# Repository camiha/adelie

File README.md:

# adelie
 44key split keyboard   
 inspired by corne, caravelle

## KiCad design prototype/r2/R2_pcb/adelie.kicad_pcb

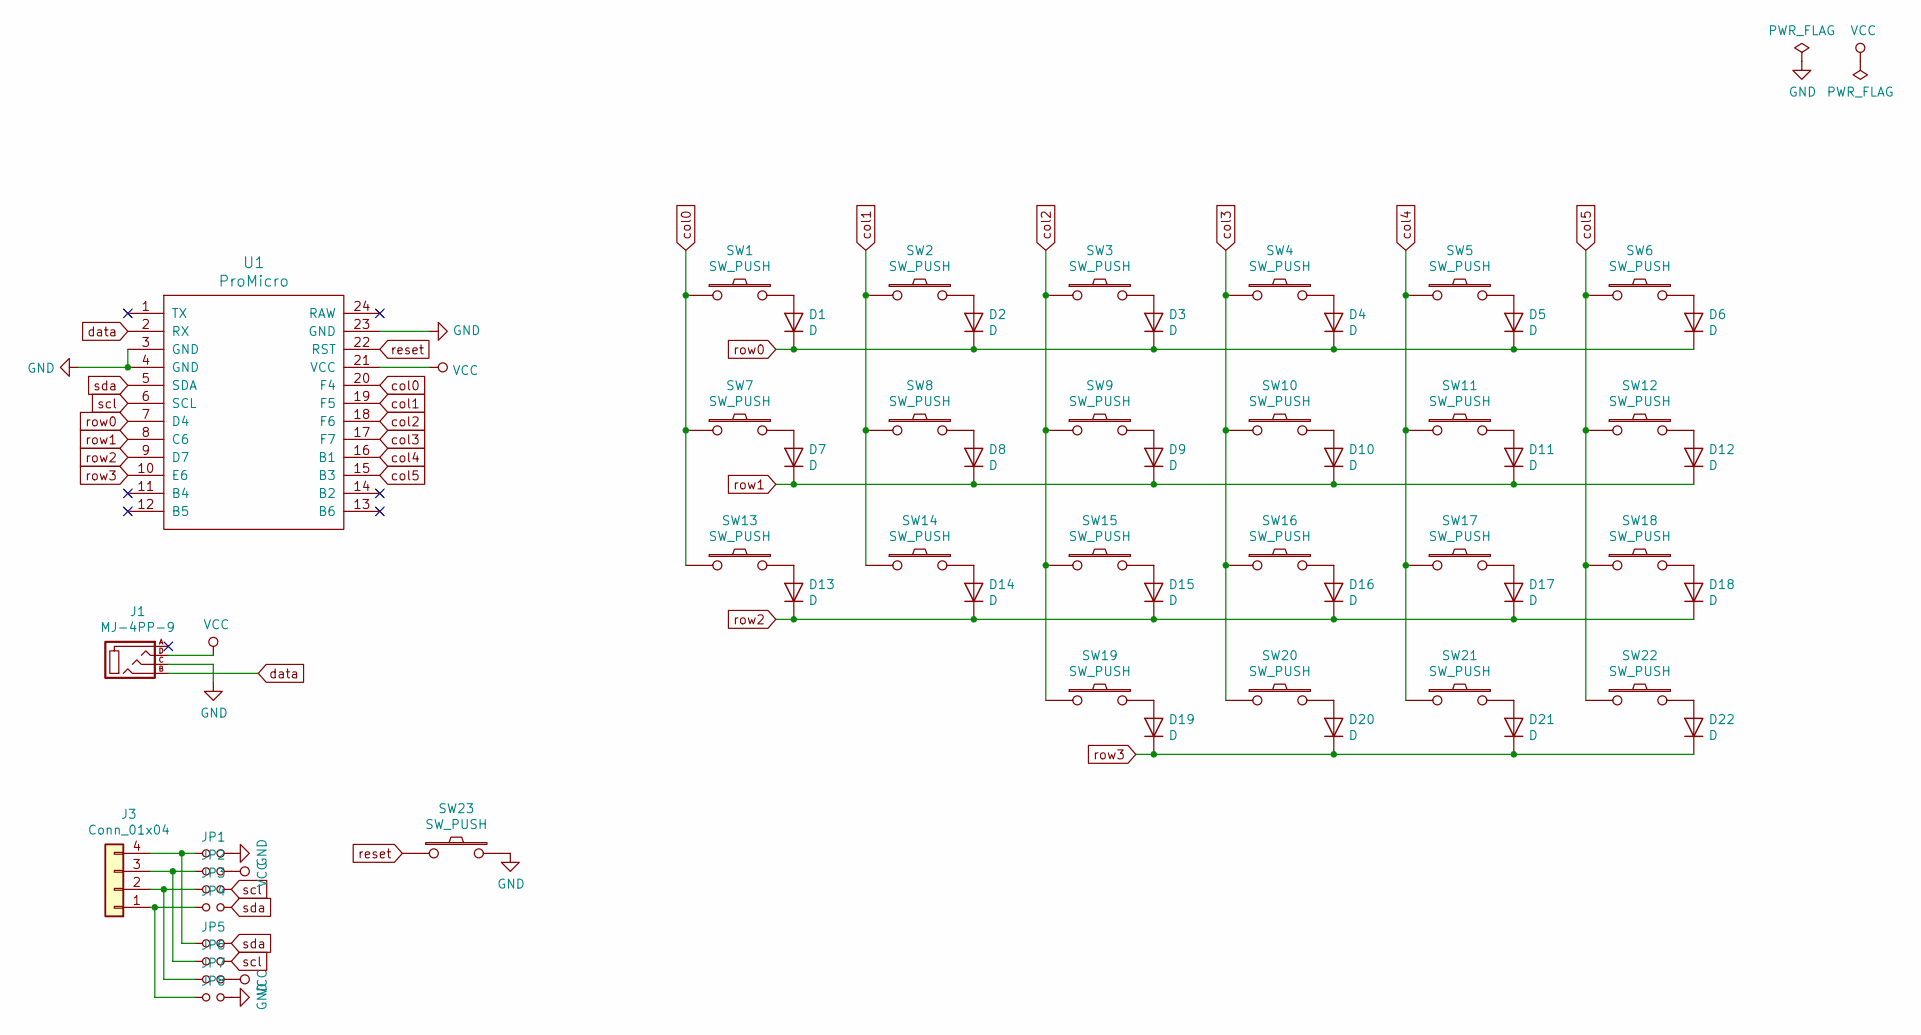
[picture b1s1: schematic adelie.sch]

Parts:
D1, D2, D3, D4, D5, D6, D7, D8, D9, D10, D11, D12, D13, D14, D15, D16, D17, D18, D19, D20, D21, D22: D; D3_SMD
J1: MJ-4PP-9
J3: Conn_01x04; OLED
JP1, JP2, JP3, JP4, JP5, JP6, JP7, JP8: Jumper_NO_Small; Jumper
SW1, SW2, SW3, SW4, SW5, SW6, SW7, SW8, SW9, SW10, SW11, SW12, SW13, SW14, SW15, SW16, SW17, SW18, SW20, SW21, SW22: SW_PUSH; CherryMX_Hotswap
SW19: SW_PUSH; CherryMX_Hotswap_1.5u
SW23: SW_PUSH; ResetSW
U1: ProMicro; ProMicro_v2

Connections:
GND: J1.C, JP1.2, JP8.2, SW23.2, U1.3 (GND), U1.4 (GND), U1.23 (GND)
unnamed: D1.2 (A), SW1.2
unnamed: D2.2 (A), SW2.2
unnamed: D3.2 (A), SW3.2
unnamed: D4.2 (A), SW4.2
unnamed: D5.2 (A), SW5.2
unnamed: D6.2 (A), SW6.2
unnamed: D7.2 (A), SW7.2
unnamed: D8.2 (A), SW8.2
unnamed: D9.2 (A), SW9.2
unnamed: D10.2 (A), SW10.2
unnamed: D11.2 (A), SW11.2
unnamed: D12.2 (A), SW12.2
unnamed: D13.2 (A), SW13.2
unnamed: D14.2 (A), SW14.2
unnamed: D15.2 (A), SW15.2
unnamed: D16.2 (A), SW16.2
unnamed: D17.2 (A), SW17.2
unnamed: D18.2 (A), SW18.2
unnamed: D19.2 (A), SW19.2
unnamed: D20.2 (A), SW20.2
unnamed: D21.2 (A), SW21.2
unnamed: D22.2 (A), SW22.2
unnamed: J3.1, JP4.1, JP8.1
unnamed: J3.2, JP3.1, JP7.1
unnamed: J3.3, JP2.1, JP6.1
unnamed: J3.4, JP1.1, JP5.1
VCC: J1.D, JP2.2, JP7.2, U1.21 (VCC)
col0: SW1.1, SW7.1, SW13.1, U1.20 (F4)
col1: SW2.1, SW8.1, SW14.1, U1.19 (F5)
col2: SW3.1, SW9.1, SW15.1, SW19.1, U1.18 (F6)
col3: SW4.1, SW10.1, SW16.1, SW20.1, U1.17 (F7)
col4: SW5.1, SW11.1, SW17.1, SW21.1, U1.16 (B1)
col5: SW6.1, SW12.1, SW18.1, SW22.1, U1.15 (B3)
data: J1.B, U1.2 (RX)
reset: SW23.1, U1.22 (RST)
row0: D1.1 (K), D2.1 (K), D3.1 (K), D4.1 (K), D5.1 (K), D6.1 (K), U1.7 (D4)
row1: D7.1 (K), D8.1 (K), D9.1 (K), D10.1 (K), D11.1 (K), D12.1 (K), U1.8 (C6)
row2: D13.1 (K), D14.1 (K), D15.1 (K), D16.1 (K), D17.1 (K), D18.1 (K), U1.9 (D7)
row3: D19.1 (K), D20.1 (K), D21.1 (K), D22.1 (K), U1.10 (E6)
scl: JP3.2, JP6.2, U1.6 (SCL)
sda: JP4.2, JP5.2, U1.5 (SDA)

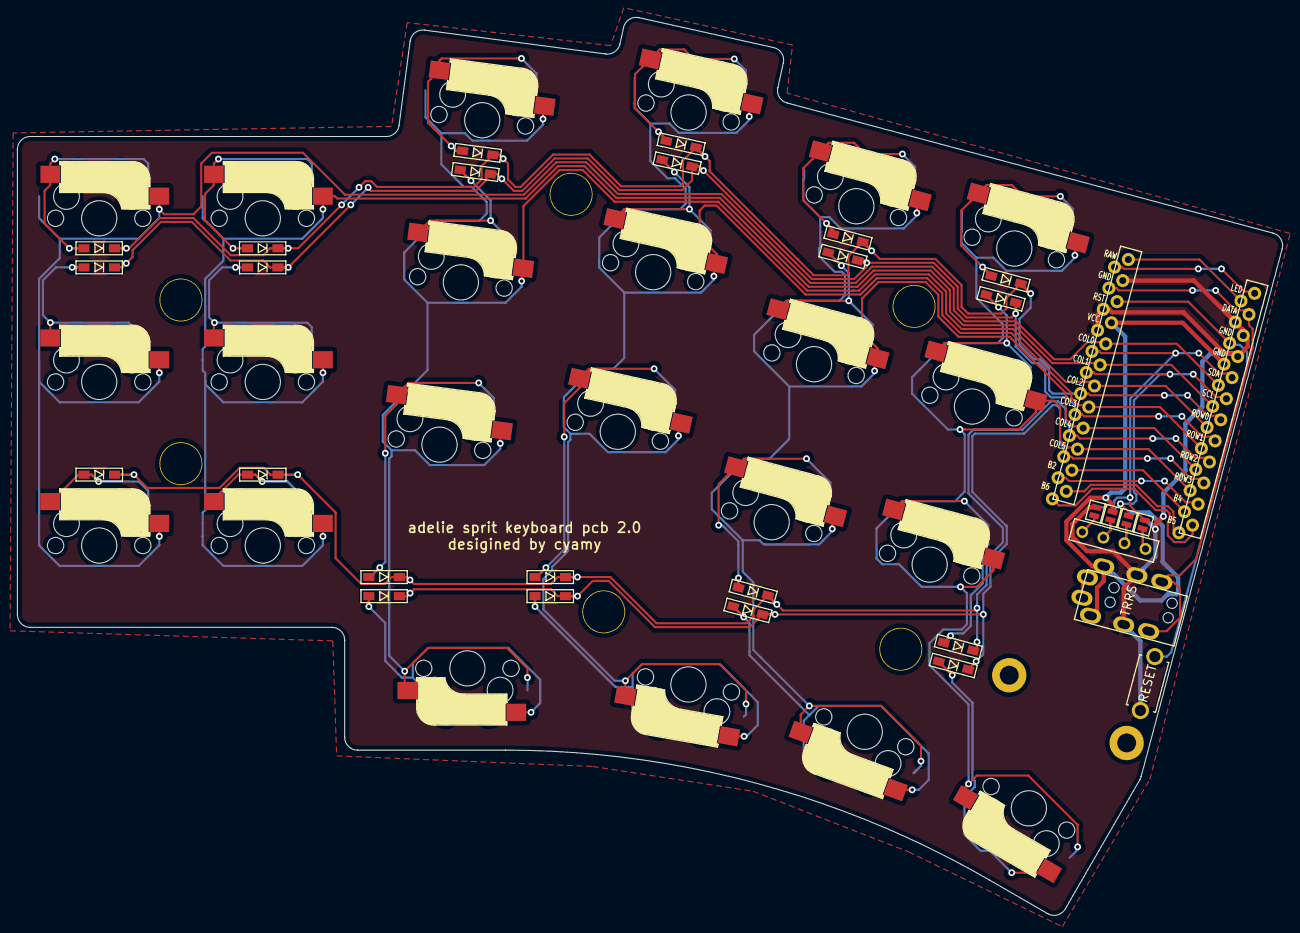
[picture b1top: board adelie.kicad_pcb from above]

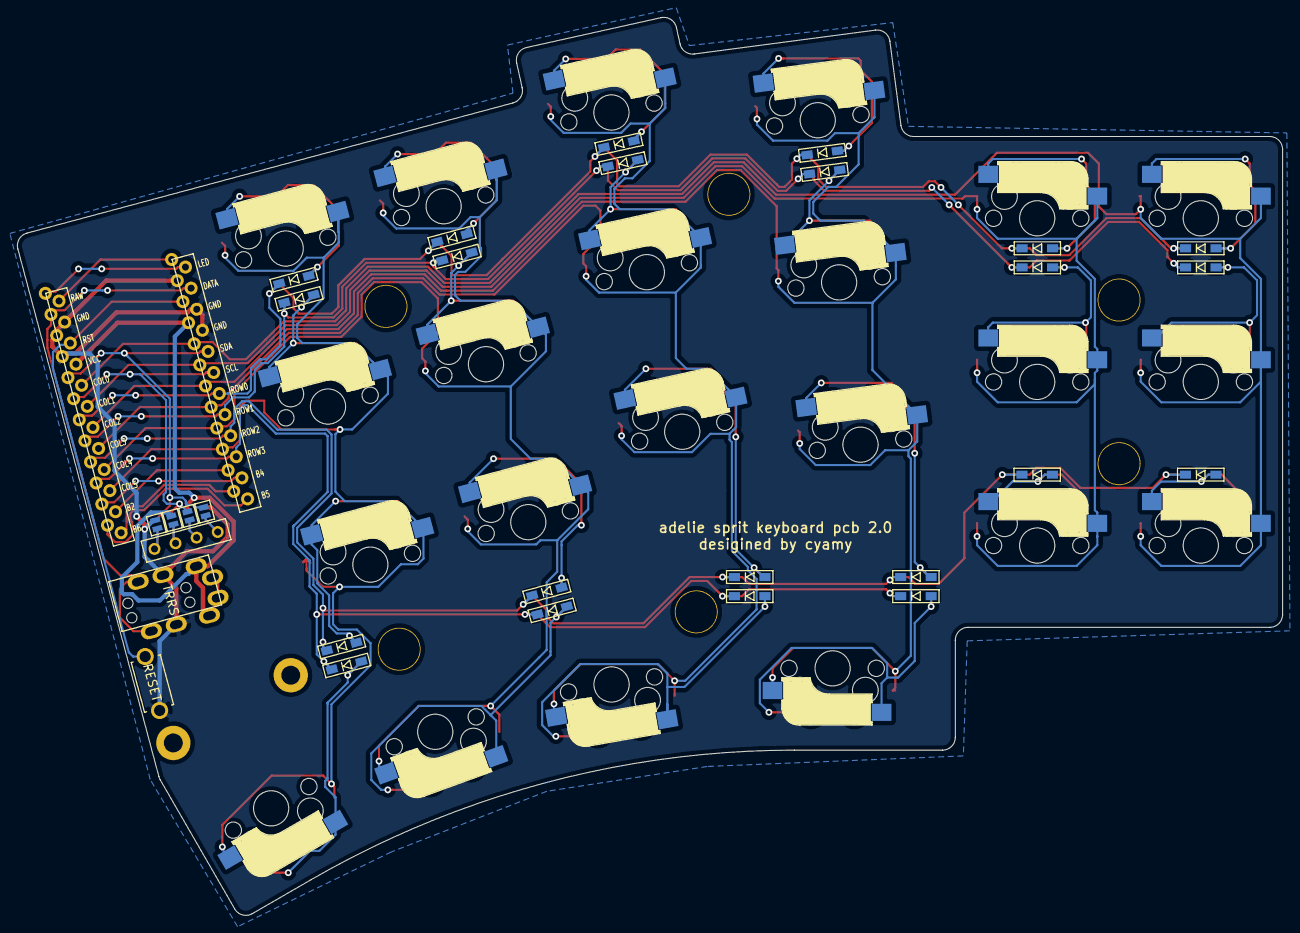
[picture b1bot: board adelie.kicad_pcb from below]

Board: 2 copper layers, 147.3 x 104.6 mm, 62 parts (4 on the bottom side), 42 nets.

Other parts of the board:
Ref**: Val**; HOLE
Ref**#2, Ref**#3, Ref**#4, Ref**#5: Val**; HOLE
e: Val**; HOLE

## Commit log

2021-03-19 readme update
2022-04-02 fix: remove images
